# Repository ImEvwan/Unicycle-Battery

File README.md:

# Unicycle Battery
This PCB is a carrier for the battery cells, making up a 12s3p bank of EVE 40PL 21700 cells. 
The PCB is meant to work with MBoards 3p nickel strip, with a tab width of 40mm.

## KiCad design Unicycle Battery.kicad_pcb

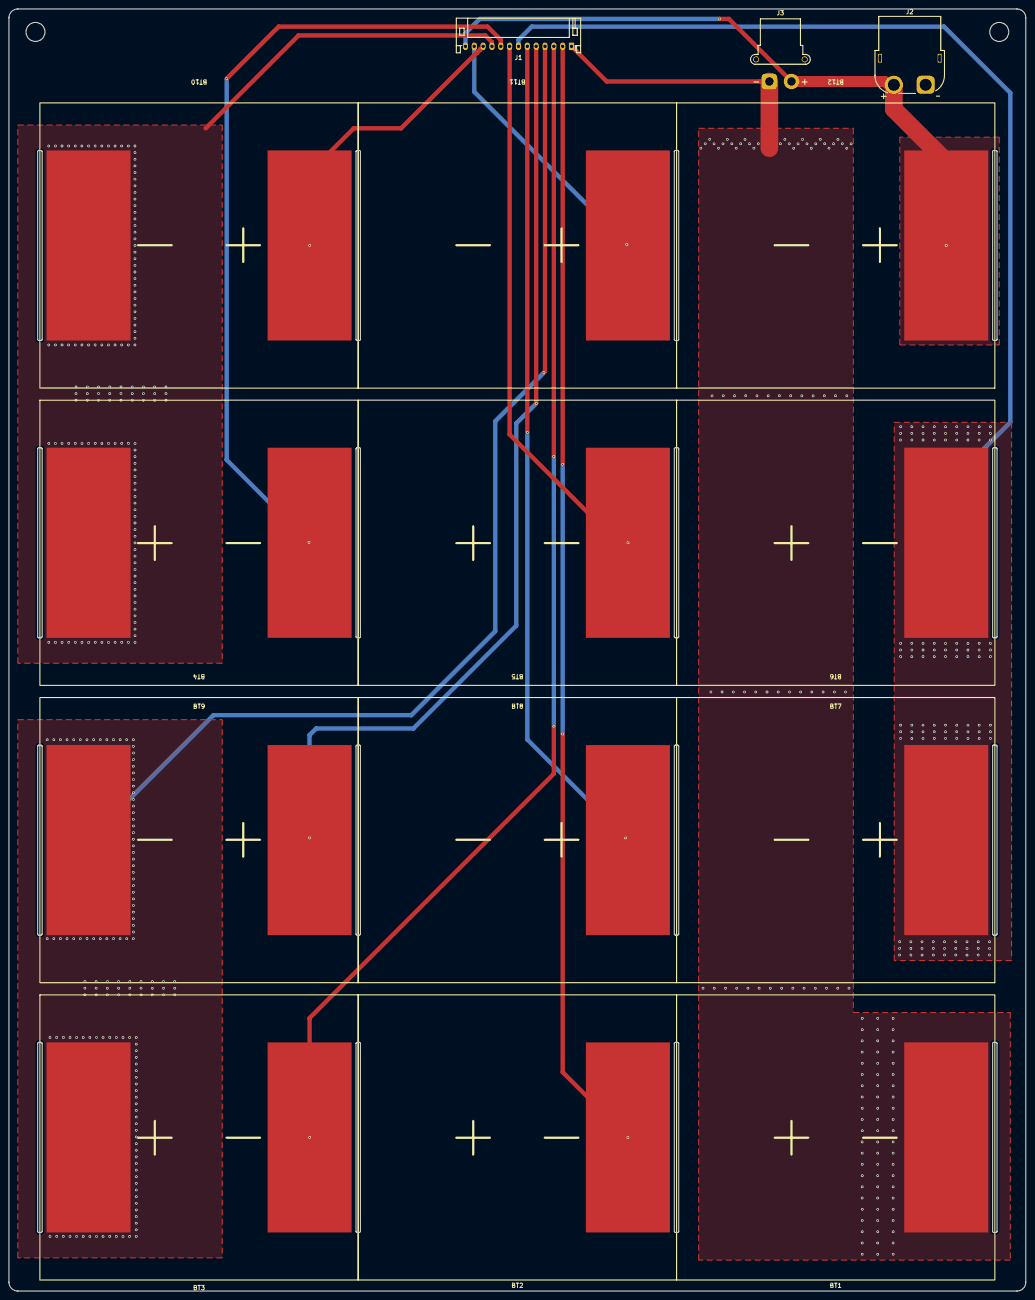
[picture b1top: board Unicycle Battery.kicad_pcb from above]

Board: 2 copper layers, 230.0 x 290.0 mm, 17 parts (0 on the bottom side), 13 nets.

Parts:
BT1, BT2, BT7, BT8: P Group Even
BT3, BT4, BT9, BT10: P Group End
BT5, BT11: P Group 4-5 10-11
BT6, BT12: P Group 5-6 11-+
H1, H2: MountingHole; MountingHole_4.3mm_M4
J1: S13B-PH-K-S; JST_PH_S13B-PH-K_1x13_P2.00mm_Horizontal
J2: XT60PW-F; AMASS_XT60PW-F_1x02_P7.20mm_Horizontal
J3: XT30PW-F; AMASS_XT30PW-F_1x02_P2.50mm_Horizontal

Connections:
+BATT: BT12.+, J1.13, J2.2, J3.2
-BATT: BT1.-, J1.1, J2.1, J3.1
/1: BT2.-, J1.2
/2: BT3.-, J1.3
/3: BT3.+, BT4.-, J1.4
/4: BT4.+, J1.5
/5: BT5.+, J1.6
/6: BT6.+, BT7.-, J1.7
/7: BT8.-, J1.8
/8: BT9.-, J1.9
/9: BT9.+, BT10.-, J1.10
/10: BT10.+, J1.11
/11: BT11.+, J1.12

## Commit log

2025-11-20 Added Library
2025-11-25 Initial Commit.
    Created P group footprint and board outline
2025-11-25 PCB Guestimate complete (tm)
2025-12-25 First draft
    Done:
    One pad per connection
    Alignment done
    All components added
    TODO:
    Via stitching
2026-03-04 Finished PCB
